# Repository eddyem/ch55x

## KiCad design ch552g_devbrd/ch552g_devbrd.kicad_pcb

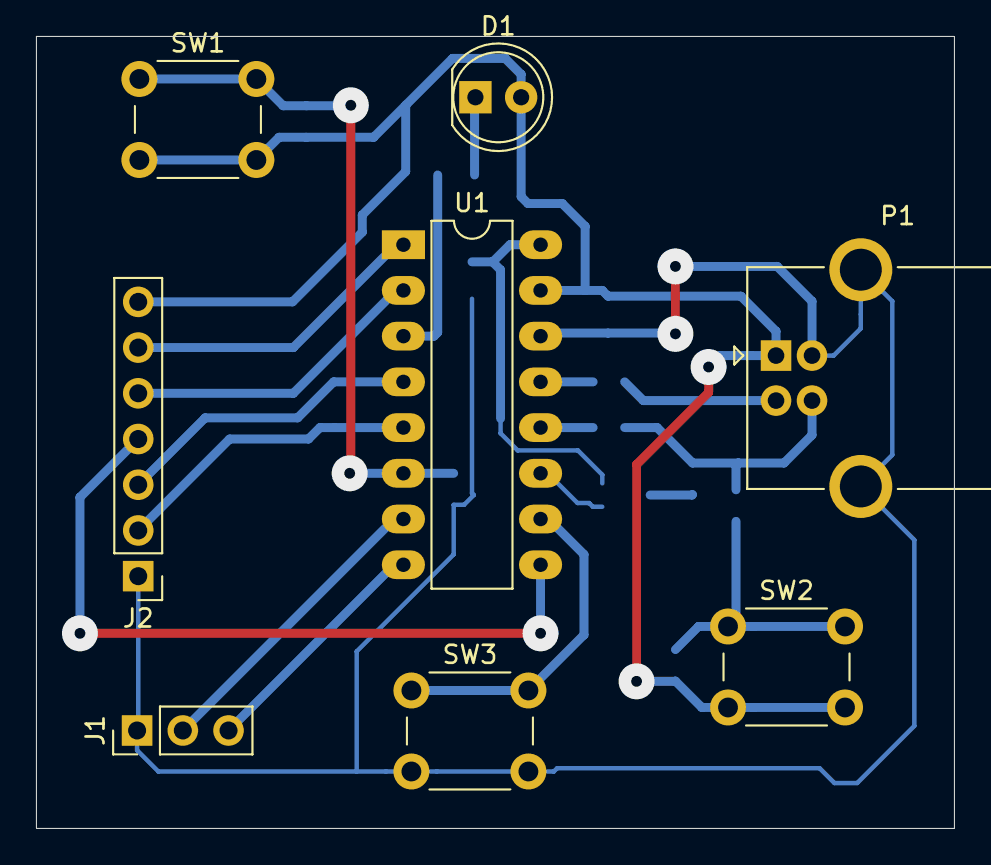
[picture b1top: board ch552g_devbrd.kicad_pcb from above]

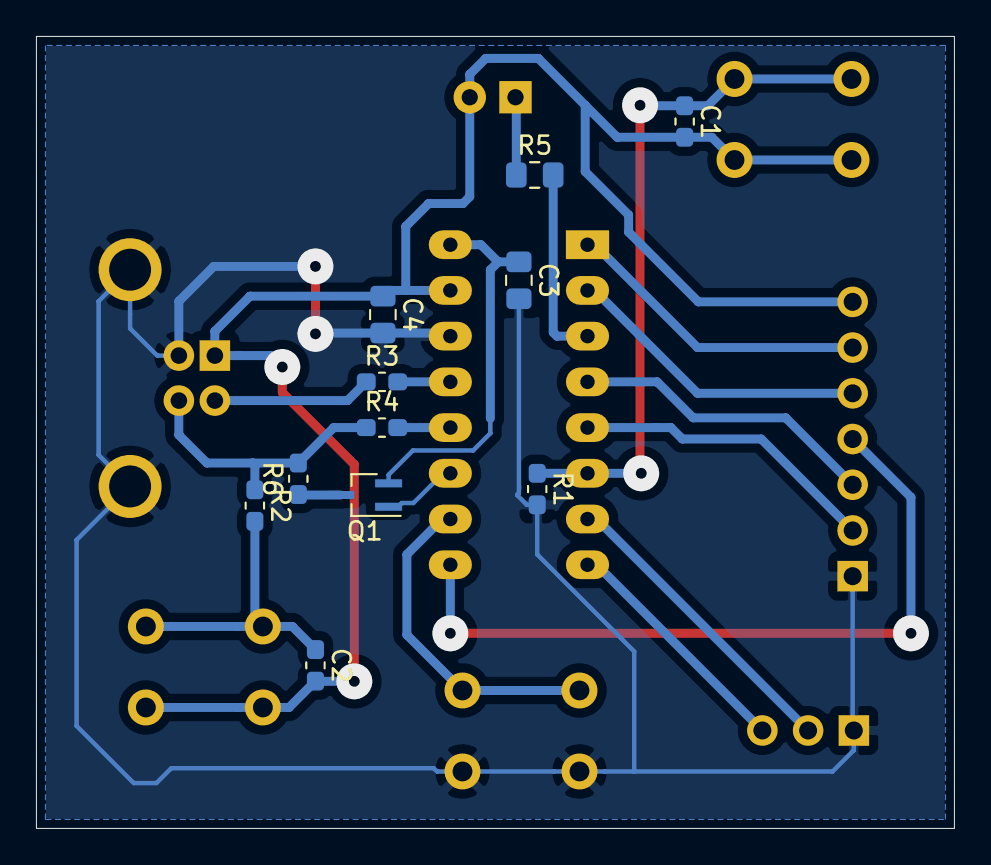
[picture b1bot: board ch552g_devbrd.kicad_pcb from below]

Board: 2 copper layers, 51.0 x 44.0 mm, 19 parts (11 on the bottom side), 21 nets.

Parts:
C1, C2: 0.1; C_0603_1608Metric_Pad1.05x0.95mm_HandSolder
C3, C4: 0.1; C_0805_2012Metric_Pad1.15x1.40mm_HandSolder
D1: LED; LED_D5.0mm
J1: USART0; PinHeader_1x03_P2.54mm_Vertical
J2: Ext; PinHeader_1x07_P2.54mm_Vertical
P1: USB_B; USB_B_OST_USB-B1HSxx_Horizontal
Q1: DTA114Y; SOT-323_SC-70_Handsoldering
R1: 10k; R_0603_1608Metric_Pad1.05x0.95mm_HandSolder
R2: 22k; R_0603_1608Metric_Pad1.05x0.95mm_HandSolder
R3, R4: 22; R_0603_1608Metric_Pad1.05x0.95mm_HandSolder
R5: 330; R_0805_2012Metric_Pad1.15x1.40mm_HandSolder
R6: 1k5; R_0603_1608Metric_Pad1.05x0.95mm_HandSolder
SW1: Reset; SW_PUSH_6mm
SW2: Prog; SW_PUSH_6mm
SW3: Button; SW_PUSH_6mm
U1: CH552G; DIP-16_W7.62mm_LongPads

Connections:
+5V: C1.2, C2.2, C4.1, D1.2, J2.7, P1.1, SW1.2, SW2.2, U1.15
/AIN: J2.6, U1.1
/BTN: SW3.1, U1.10
/CAP1: J2.5, U1.2
/CAP2: J2.4, U1.9
/LED_PWM: R5.2, U1.3
/RST: C1.1, R1.1, SW1.1, U1.6
/Rxd: J1.3, U1.8
/Touch0: J2.3, U1.4
/Touch1: J2.2, U1.5
/Txd: J1.2, U1.7
/UDM: R3.2, U1.13
/UDP: R4.2, U1.12
/UDP_PU: Q1.1, U1.11
/UDPbt: P1.3, R2.1, R4.1, R6.2
/V33: C3.1, Q1.2, U1.16
GND: C3.2, C4.2, J1.1, J2.1, P1.4, P1.5, R1.2, SW3.2, U1.14
unnamed: C2.1, R2.2, SW2.1
unnamed: D1.1, R5.1
unnamed: P1.2, R3.1
unnamed: Q1.3, R6.1

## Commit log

2020-11-15 Initial commit: ch55xtool
2020-11-19 start adding examples
